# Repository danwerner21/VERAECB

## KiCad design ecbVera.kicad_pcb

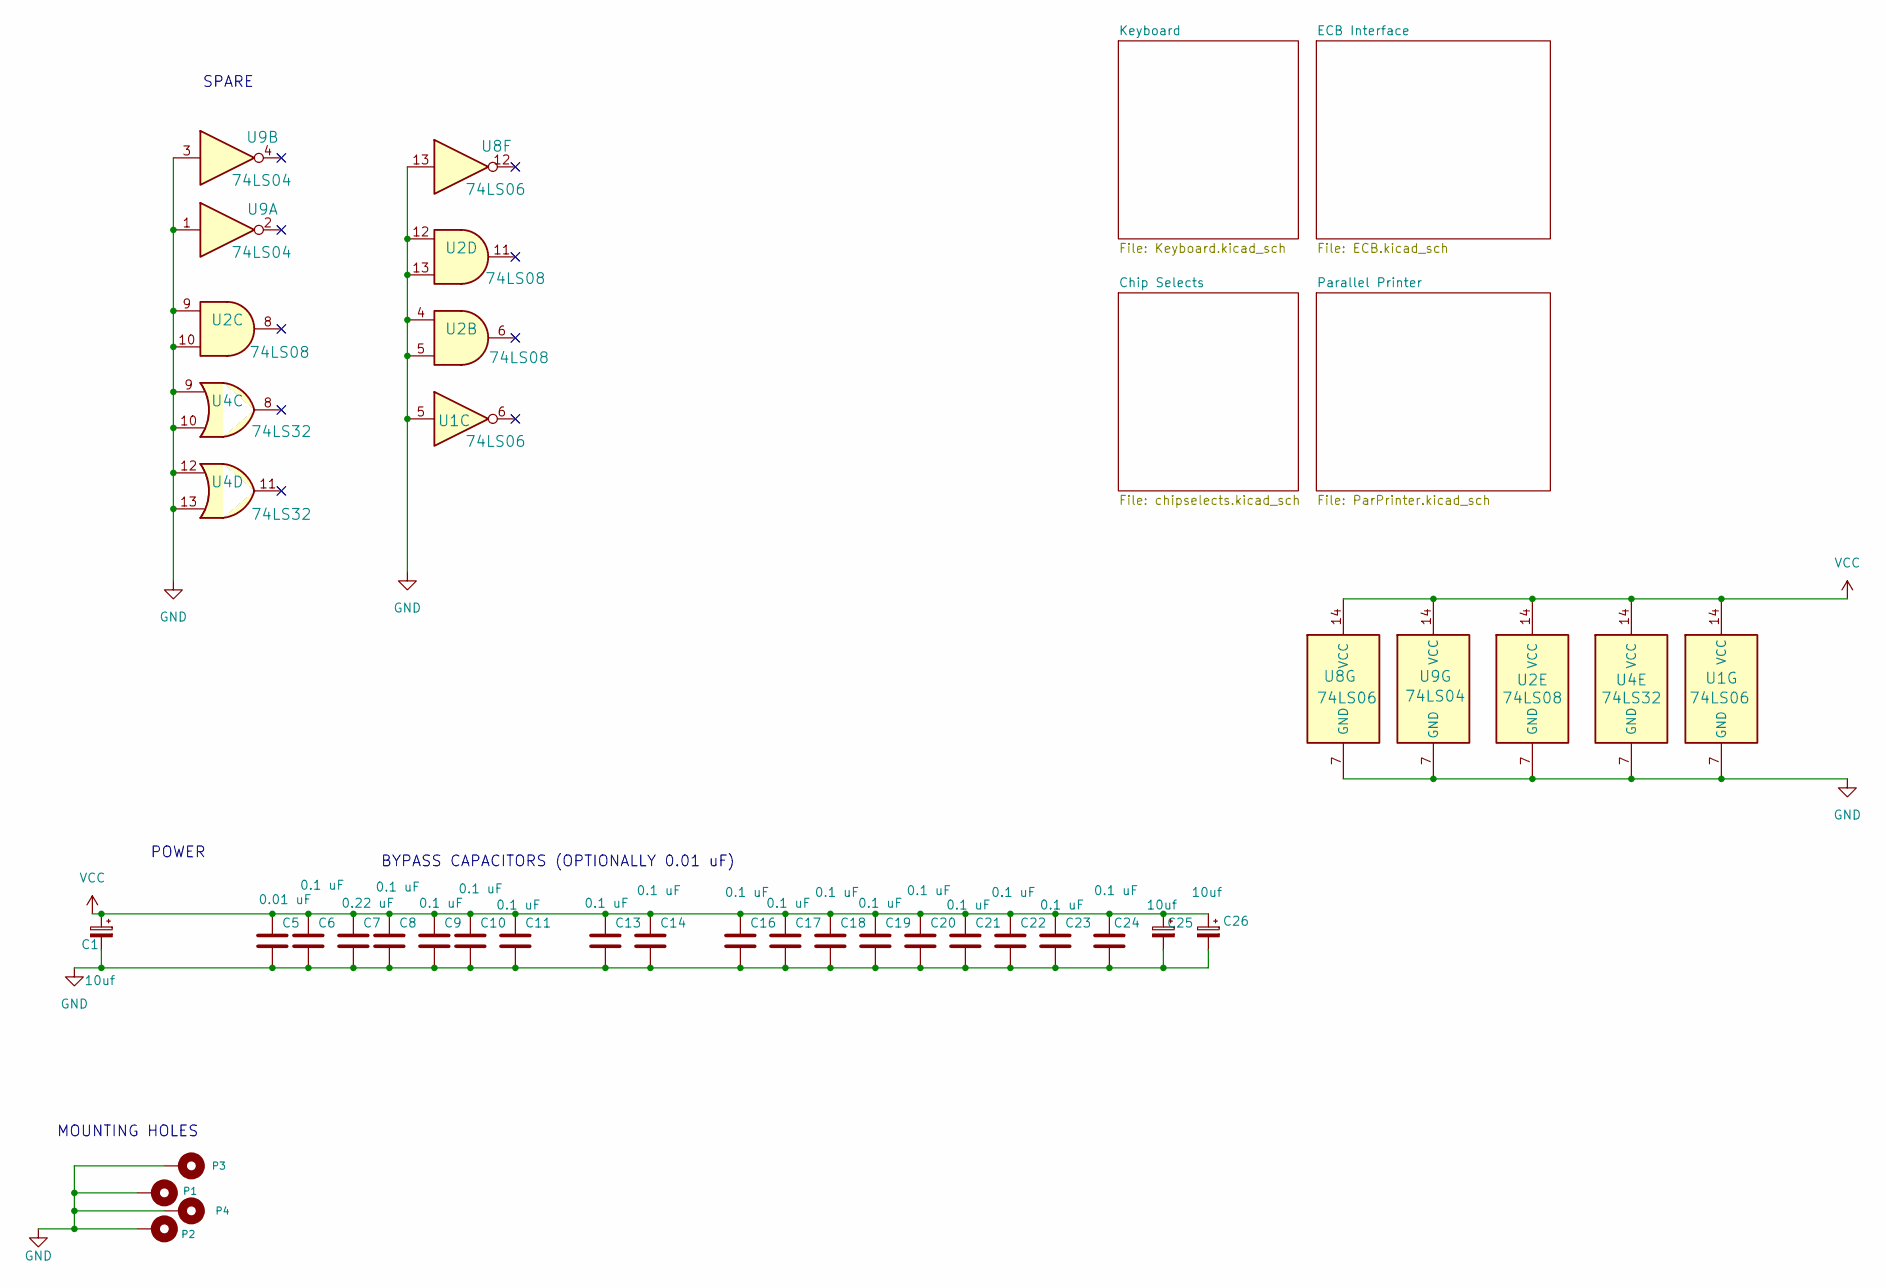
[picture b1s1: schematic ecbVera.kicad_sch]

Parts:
C1, C25, C26: 10uf; STD_DDW_PCAP
C5: 0.01 uF; STD_DDW_CAP
C6, C8, C9, C10, C11, C13, C14, C16, C17, C18, C19, C20, C21, C22, C23, C24: 0.1 uF; STD_DDW_CAP
C7: 0.22 uF; STD_DDW_CAP
P1, P2, P3, P4: MountingHole_4.3mm_M4
U1, U8: 74LS06; STD_DDW_DIP14
U2: 74LS08; STD_DDW_DIP14
U4: 74LS32; STD_DDW_DIP14
U9: 74LS04; STD_DDW_DIP14

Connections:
GND: C1.2, C5.2, C6.2, C7.2, C8.2, C9.2, C10.2, C11.2, C13.2, C14.2, C16.2, C17.2, C18.2, C19.2, C20.2, C21.2, C22.2, C23.2, C24.2, C25.2, C26.2, P1.1, P2.1, P3.1, P4.1, U1.5, U1.7 (GND), U2.4, U2.5, U2.7 (GND), U2.9, U2.10, U2.12, U2.13, U4.7 (GND), U4.9, U4.10, U4.12, U4.13, U8.7 (GND), U8.13, U9.1, U9.3, U9.7 (GND); also elsewhere on the board
VCC: C1.1, C5.1, C6.1, C7.1, C8.1, C9.1, C10.1, C11.1, C13.1, C14.1, C16.1, C17.1, C18.1, C19.1, C20.1, C21.1, C22.1, C23.1, C24.1, C25.1, C26.1, U1.14 (VCC), U2.14 (VCC), U4.14 (VCC), U8.14 (VCC), U9.14 (VCC); also elsewhere on the board

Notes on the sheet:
SPARE
MOUNTING HOLES
BYPASS CAPACITORS (OPTIONALLY 0.01 uF)
POWER

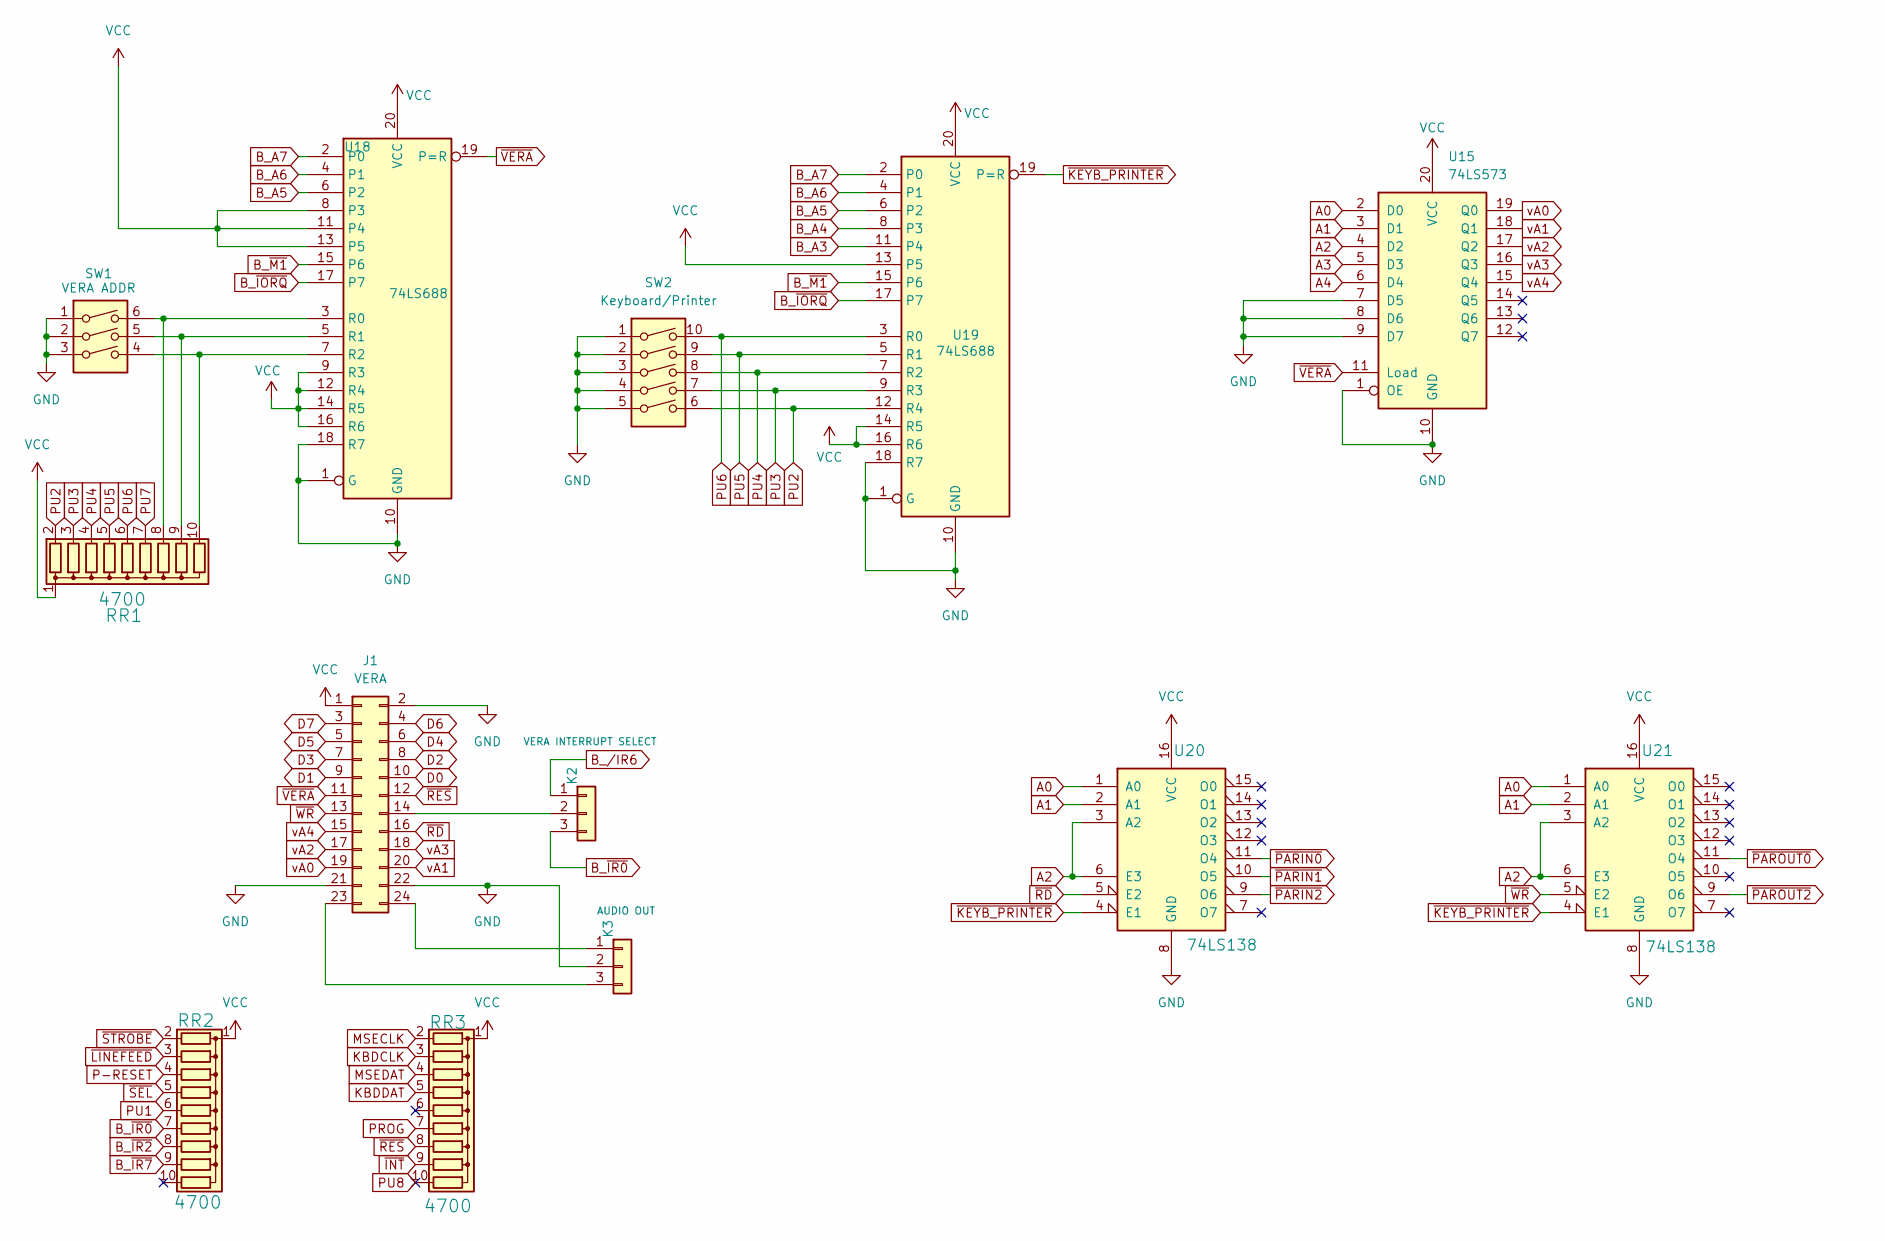
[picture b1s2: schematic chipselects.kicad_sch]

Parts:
J1: VERA; PinHeader_2x12_P2.54mm_Vertical
K2: VERA INTERRUPT SELECT; STD_DDW_PINHEAD_V_1x03
K3: AUDIO OUT; STD_DDW_PINHEAD_V_1x03
RR1, RR2, RR3: 4700; R_Array_SIP10
SW1: VERA ADDR; STD_DDW_DIP6
SW2: Keyboard/Printer; STD_DDW_DIP10
U15: 74LS573; STD_DDW_DIP20
U18, U19: 74LS688; STD_DDW_DIP20
U20, U21: 74LS138; STD_DDW_DIP16

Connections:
A0: U15.2 (D0), U20.1 (A0), U21.1 (A0); also elsewhere on the board
A1: U15.3 (D1), U20.2 (A1), U21.2 (A1); also elsewhere on the board
A2: U15.4 (D2), U20.3 (A2), U20.6 (E3), U21.3 (A2), U21.6 (E3); also elsewhere on the board
A3: U15.5 (D3); also elsewhere on the board
A4: U15.6 (D4); also elsewhere on the board
B_A3: U19.11 (P4); also elsewhere on the board
B_A4: U19.8 (P3); also elsewhere on the board
B_A5: U18.6 (P2), U19.6 (P2); also elsewhere on the board
B_A6: U18.4 (P1), U19.4 (P1); also elsewhere on the board
B_A7: U18.2 (P0), U19.2 (P0); also elsewhere on the board
B_~IORQ: U18.17 (P7), U19.17 (P7); also elsewhere on the board
B_~IR0: K2.3, RR2.7 (R6); also elsewhere on the board
B_~IR2: RR2.8 (R7); also elsewhere on the board
B_~IR7: RR2.9 (R8); also elsewhere on the board
B_~M1: U18.15 (P6), U19.15 (P6); also elsewhere on the board
D0: J1.10; also elsewhere on the board
D1: J1.9; also elsewhere on the board
D2: J1.8; also elsewhere on the board
D3: J1.7; also elsewhere on the board
D4: J1.6; also elsewhere on the board
D5: J1.5; also elsewhere on the board
D6: J1.4; also elsewhere on the board
D7: J1.3; also elsewhere on the board
GND: J1.2, J1.21, J1.22, K3.2, SW1.1, SW1.2, SW1.3, SW2.1, SW2.2, SW2.3, SW2.4, SW2.5, U15.1 (OE), U15.7 (D5), U15.8 (D6), U15.9 (D7), U15.10 (GND), U18.1 (G), U18.10 (GND), U18.18 (R7), U19.1 (G), U19.10 (GND), U19.18 (R7), U20.8 (GND), U21.8 (GND); also elsewhere on the board
KBDCLK: RR3.3 (R2); also elsewhere on the board
KBDDAT: RR3.5 (R4); also elsewhere on the board
MSECLK: RR3.2 (R1); also elsewhere on the board
MSEDAT: RR3.4 (R3); also elsewhere on the board
unnamed: J1.14, K2.2
unnamed: J1.23, K3.3
unnamed: J1.24, K3.1
unnamed: RR1.8 (R7), SW1.6, U18.3 (R0)
unnamed: RR1.9 (R8), SW1.5, U18.5 (R1)
unnamed: RR1.10 (R9), SW1.4, U18.7 (R2)
P-RESET: RR2.4 (R3); also elsewhere on the board
PROG: RR3.7 (R6); also elsewhere on the board
PU1: RR2.6 (R5); also elsewhere on the board
PU2: RR1.2 (R1), SW2.6, U19.12 (R4)
PU3: RR1.3 (R2), SW2.7, U19.9 (R3)
PU4: RR1.4 (R3), SW2.8, U19.7 (R2)
PU5: RR1.5 (R4), SW2.9, U19.5 (R1)
PU6: RR1.6 (R5), SW2.10, U19.3 (R0)
PU7: RR1.7 (R6); also elsewhere on the board
PU8: RR3.10 (R9)
VCC: J1.1, RR1.1 (common), RR2.1 (common), RR3.1 (common), U15.20 (VCC), U18.8 (P3), U18.9 (R3), U18.11 (P4), U18.12 (R4), U18.13 (P5), U18.14 (R5), U18.16 (R6), U18.20 (VCC), U19.13 (P5), U19.14 (R5), U19.16 (R6), U19.20 (VCC), U20.16 (VCC), U21.16 (VCC); also elsewhere on the board
vA0: J1.19, U15.19 (Q0)
vA1: J1.20, U15.18 (Q1)
vA2: J1.17, U15.17 (Q2)
vA3: J1.18, U15.16 (Q3)
vA4: J1.15, U15.15 (Q4)
~INT: RR3.9 (R8); also elsewhere on the board
~KEYB_PRINTER: U19.19 (P=R), U20.4 (E1), U21.4 (E1); also elsewhere on the board
~LINEFEED: RR2.3 (R2); also elsewhere on the board
~PARIN0: U20.11 (O4); also elsewhere on the board
~PARIN1: U20.10 (O5); also elsewhere on the board
~PARIN2: U20.9 (O6); also elsewhere on the board
~PAROUT0: U21.11 (O4); also elsewhere on the board
~PAROUT2: U21.9 (O6); also elsewhere on the board
~RD: J1.16, U20.5 (E2); also elsewhere on the board
~RES: J1.12, RR3.8 (R7); also elsewhere on the board
~SEL: RR2.5 (R4); also elsewhere on the board
~STROBE: RR2.2 (R1); also elsewhere on the board
~VERA: J1.11, U15.11 (Load), U18.19 (P=R); also elsewhere on the board
~WR: J1.13, U21.5 (E2); also elsewhere on the board

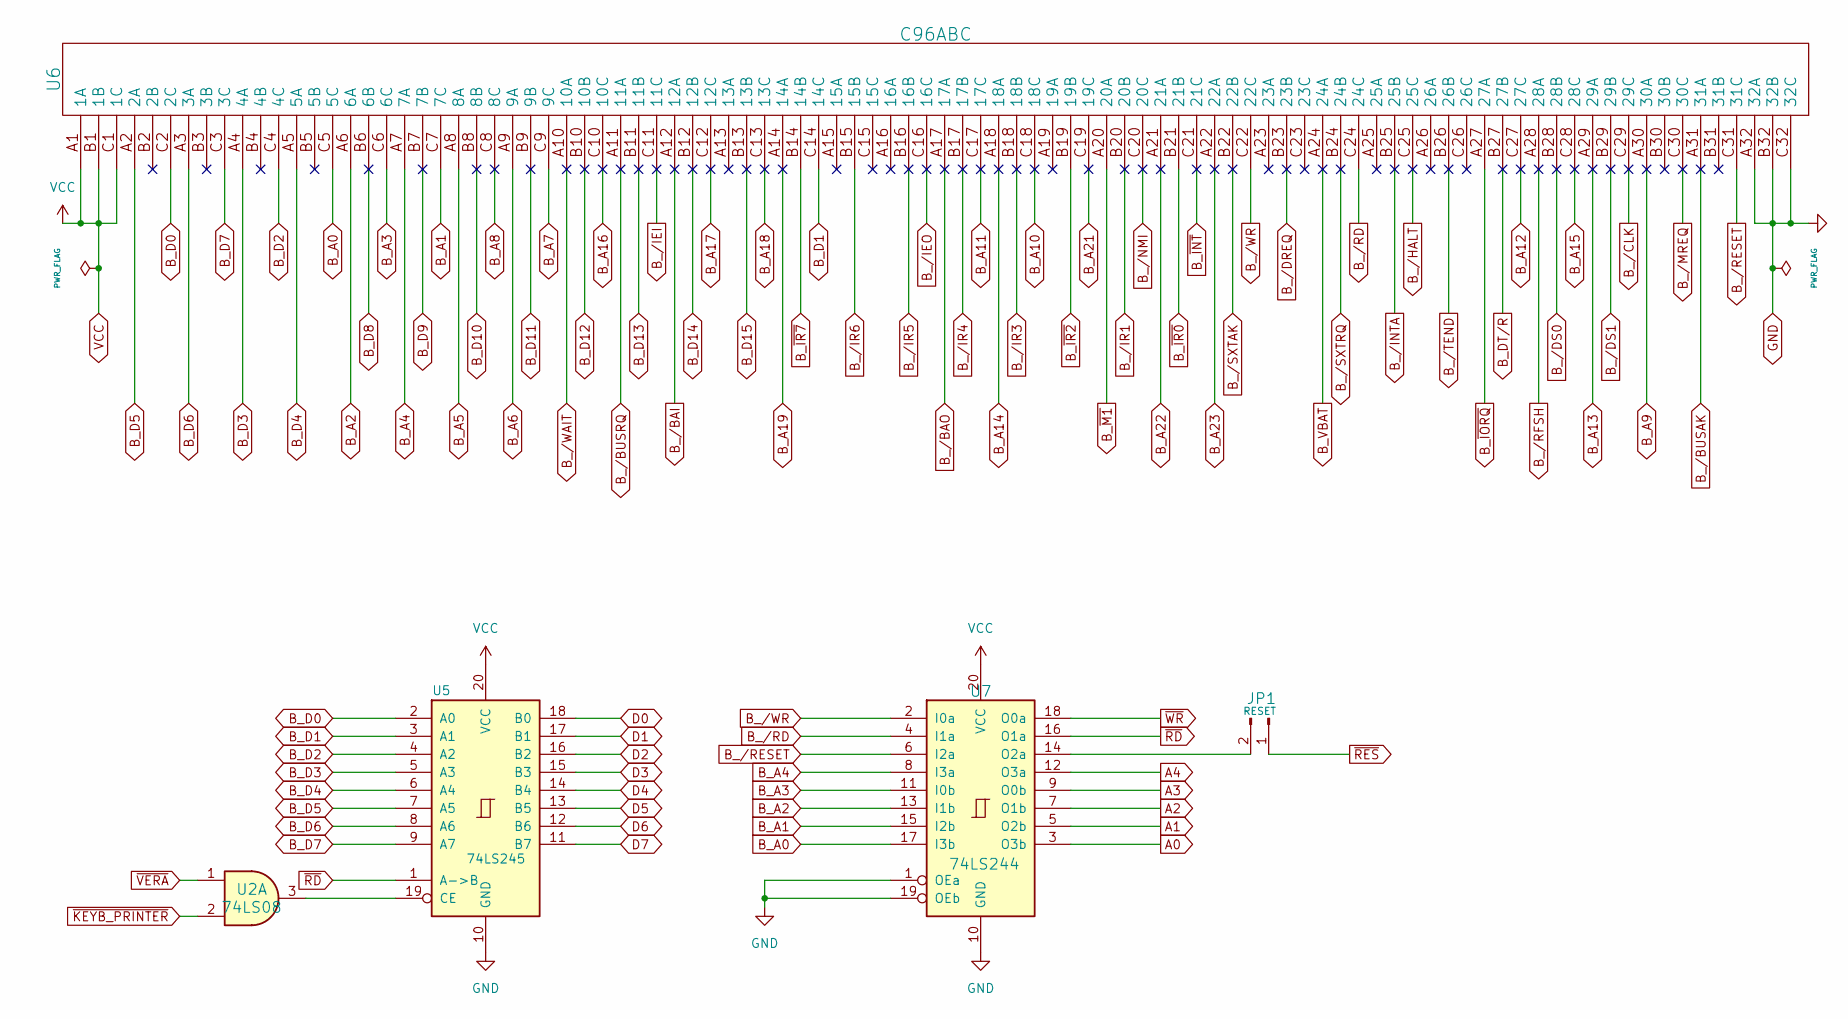
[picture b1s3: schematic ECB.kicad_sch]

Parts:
JP1: RESET; STD_DDW_PINHEAD_V_1x02
U2: 74LS08; STD_DDW_DIP14
U5: 74LS245; STD_DDW_DIP20
U6: C96ABC
U7: 74LS244; STD_DDW_DIP20

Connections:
A0: U7.3 (O3b); also elsewhere on the board
A1: U7.5 (O2b); also elsewhere on the board
A2: U7.7 (O1b); also elsewhere on the board
A3: U7.9 (O0b); also elsewhere on the board
A4: U7.12 (O3a); also elsewhere on the board
B_A0: U6.C5 (5C), U7.17 (I3b)
B_A1: U6.C7 (7C), U7.15 (I2b)
B_A2: U6.A6 (6A), U7.13 (I1b); also elsewhere on the board
B_A3: U6.C6 (6C), U7.11 (I0b); also elsewhere on the board
B_A4: U6.A7 (7A), U7.8 (I3a); also elsewhere on the board
B_A5: U6.A8 (8A); also elsewhere on the board
B_A6: U6.A9 (9A); also elsewhere on the board
B_A7: U6.C9 (9C); also elsewhere on the board
B_A8: U6.C8 (8C)
B_A9: U6.A30 (30A)
B_A10: U6.C18 (18C)
B_A11: U6.C17 (17C)
B_A12: U6.C27 (27C)
B_A13: U6.A29 (29A)
B_A14: U6.A18 (18A)
B_A15: U6.C28 (28C)
B_A16: U6.C10 (10C)
B_A17: U6.C12 (12C)
B_A18: U6.C13 (13C)
B_A19: U6.A14 (14A)
B_A21: U6.C19 (19C)
B_A22: U6.A21 (21A)
B_A23: U6.A22 (22A)
B_D0: U5.2 (A0), U6.C2 (2C)
B_D1: U5.3 (A1), U6.C14 (14C)
B_D2: U5.4 (A2), U6.C4 (4C)
B_D3: U5.5 (A3), U6.A4 (4A)
B_D4: U5.6 (A4), U6.A5 (5A)
B_D5: U5.7 (A5), U6.A2 (2A)
B_D6: U5.8 (A6), U6.A3 (3A)
B_D7: U5.9 (A7), U6.C3 (3C)
B_D8: U6.B6 (6B)
B_D9: U6.B7 (7B)
B_D10: U6.B8 (8B)
B_D11: U6.B9 (9B)
B_D12: U6.B10 (10B)
B_D13: U6.B11 (11B)
B_D14: U6.B12 (12B)
B_D15: U6.B13 (13B)
B_DT/R: U6.B27 (27B)
B_VBAT: U6.A24 (24A)
B_/BAI: U6.A12 (12A)
B_/BAO: U6.A17 (17A)
B_/BUSAK: U6.A31 (31A)
B_/BUSRQ: U6.A11 (11A)
B_/CLK: U6.C29 (29C)
B_/DREQ: U6.B23 (23B)
B_/DS0: U6.B28 (28B)
B_/DS1: U6.B29 (29B)
B_/HALT: U6.C25 (25C)
B_/IEI: U6.C11 (11C)
B_/IEO: U6.C16 (16C)
B_/INTA: U6.B25 (25B)
B_/IR1: U6.B20 (20B)
B_/IR3: U6.B18 (18B)
B_/IR4: U6.B17 (17B)
B_/IR5: U6.B16 (16B)
B_/MREQ: U6.C30 (30C)
B_/NMI: U6.C20 (20C)
B_/RFSH: U6.A28 (28A)
B_/SXTAK: U6.B22 (22B)
B_/SXTRQ: U6.B24 (24B)
B_/TEND: U6.B26 (26B)
B_/WAIT: U6.A10 (10A)
B_~INT: U6.C21 (21C)
B_~IORQ: U6.A27 (27A); also elsewhere on the board
B_~IR0: U6.B21 (21B); also elsewhere on the board
B_~IR2: U6.B19 (19B); also elsewhere on the board
B_~IR7: U6.B14 (14B); also elsewhere on the board
B_~M1: U6.A20 (20A); also elsewhere on the board
D0: U5.18 (B0); also elsewhere on the board
D1: U5.17 (B1); also elsewhere on the board
D2: U5.16 (B2); also elsewhere on the board
D3: U5.15 (B3); also elsewhere on the board
D4: U5.14 (B4); also elsewhere on the board
D5: U5.13 (B5); also elsewhere on the board
D6: U5.12 (B6); also elsewhere on the board
D7: U5.11 (B7); also elsewhere on the board
GND: U5.10 (GND), U6.A32 (32A), U6.B32 (32B), U6.C32 (32C), U7.1 (OEa), U7.10 (GND), U7.19 (OEb); also elsewhere on the board
unnamed: JP1.2, U7.14 (O2a)
unnamed: U2.3, U5.19 (CE)
VCC: U5.20 (VCC), U6.A1 (1A), U6.B1 (1B), U6.C1 (1C), U7.20 (VCC); also elsewhere on the board
~KEYB_PRINTER: U2.2; also elsewhere on the board
~RD: U5.1 (A->B), U7.16 (O1a); also elsewhere on the board
~RES: JP1.1; also elsewhere on the board
~VERA: U2.1; also elsewhere on the board
~WR: U7.18 (O0a); also elsewhere on the board

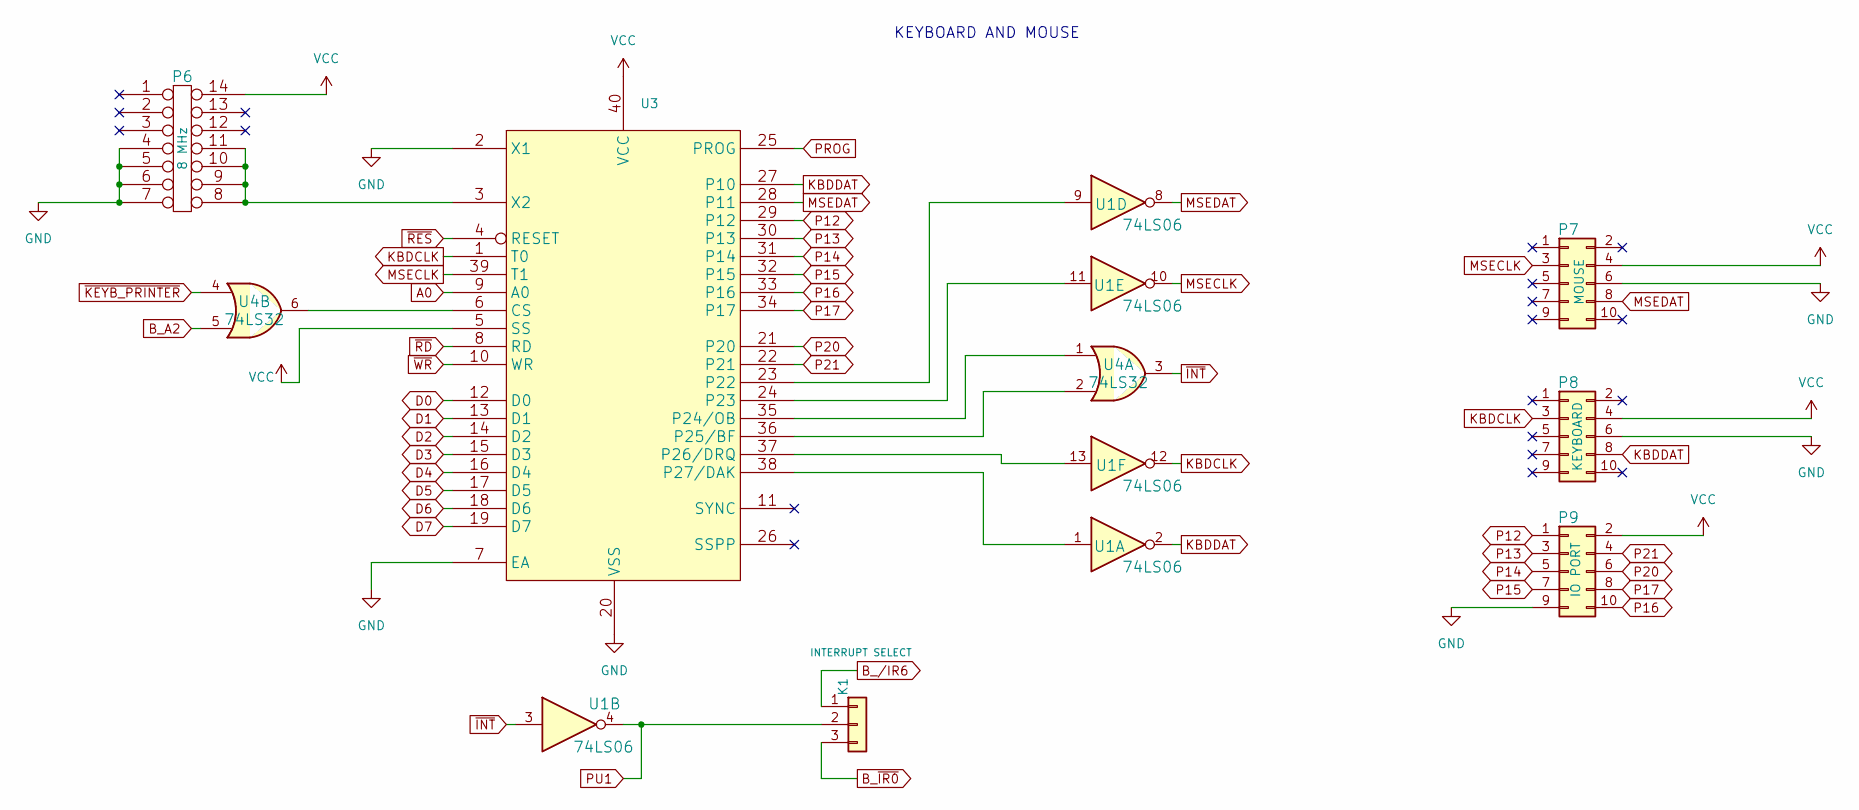
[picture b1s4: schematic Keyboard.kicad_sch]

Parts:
K1: INTERRUPT SELECT; STD_DDW_PINHEAD_V_1x03
P6: 8 MHz; STD_DDW_DIP14
P7: MOUSE; STD_DDW_PINHEAD_V_2x05
P8: KEYBOARD; STD_DDW_PINHEAD_V_2x05
P9: IO PORT; STD_DDW_PINHEAD_V_2x05
U1: 74LS06; STD_DDW_DIP14
U3: STD_DDW_DIP40
U4: 74LS32; STD_DDW_DIP14

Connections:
A0: U3.9 (A0); also elsewhere on the board
B_A2: U4.5; also elsewhere on the board
B_~IR0: K1.3; also elsewhere on the board
D0: U3.12 (D0); also elsewhere on the board
D1: U3.13 (D1); also elsewhere on the board
D2: U3.14 (D2); also elsewhere on the board
D3: U3.15 (D3); also elsewhere on the board
D4: U3.16 (D4); also elsewhere on the board
D5: U3.17 (D5); also elsewhere on the board
D6: U3.18 (D6); also elsewhere on the board
D7: U3.19 (D7); also elsewhere on the board
GND: P6.4, P6.5, P6.6, P6.7, P7.6, P8.6, P9.9, U3.2 (X1), U3.7 (EA), U3.20 (VSS); also elsewhere on the board
KBDCLK: P8.3, U1.12, U3.1 (T0); also elsewhere on the board
KBDDAT: P8.8, U1.2, U3.27 (P10); also elsewhere on the board
MSECLK: P7.3, U1.10, U3.39 (T1); also elsewhere on the board
MSEDAT: P7.8, U1.8, U3.28 (P11); also elsewhere on the board
unnamed: U3.6 (CS), U4.6
unnamed: U1.9, U3.23 (P22)
unnamed: U1.11, U3.24 (P23)
unnamed: U3.35 (P24/OB), U4.1
unnamed: U3.36 (P25/BF), U4.2
unnamed: U1.13, U3.37 (P26/DRQ)
unnamed: U1.1, U3.38 (P27/DAK)
unnamed: P6.8, P6.9, P6.10, P6.11, U3.3 (X2)
P12: P9.1, U3.29 (P12)
P13: P9.3, U3.30 (P13)
P14: P9.5, U3.31 (P14)
P15: P9.7, U3.32 (P15)
P16: P9.10, U3.33 (P16)
P17: P9.8, U3.34 (P17)
P20: P9.6, U3.21 (P20)
P21: P9.4, U3.22 (P21)
PROG: U3.25 (PROG); also elsewhere on the board
PU1: K1.2, U1.4; also elsewhere on the board
VCC: P6.14, P7.4, P8.4, P9.2, U3.5 (SS), U3.40 (VCC); also elsewhere on the board
~INT: U1.3, U4.3; also elsewhere on the board
~KEYB_PRINTER: U4.4; also elsewhere on the board
~RD: U3.8 (RD); also elsewhere on the board
~RES: U3.4 (RESET); also elsewhere on the board
~WR: U3.10 (WR); also elsewhere on the board

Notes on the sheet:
KEYBOARD AND MOUSE

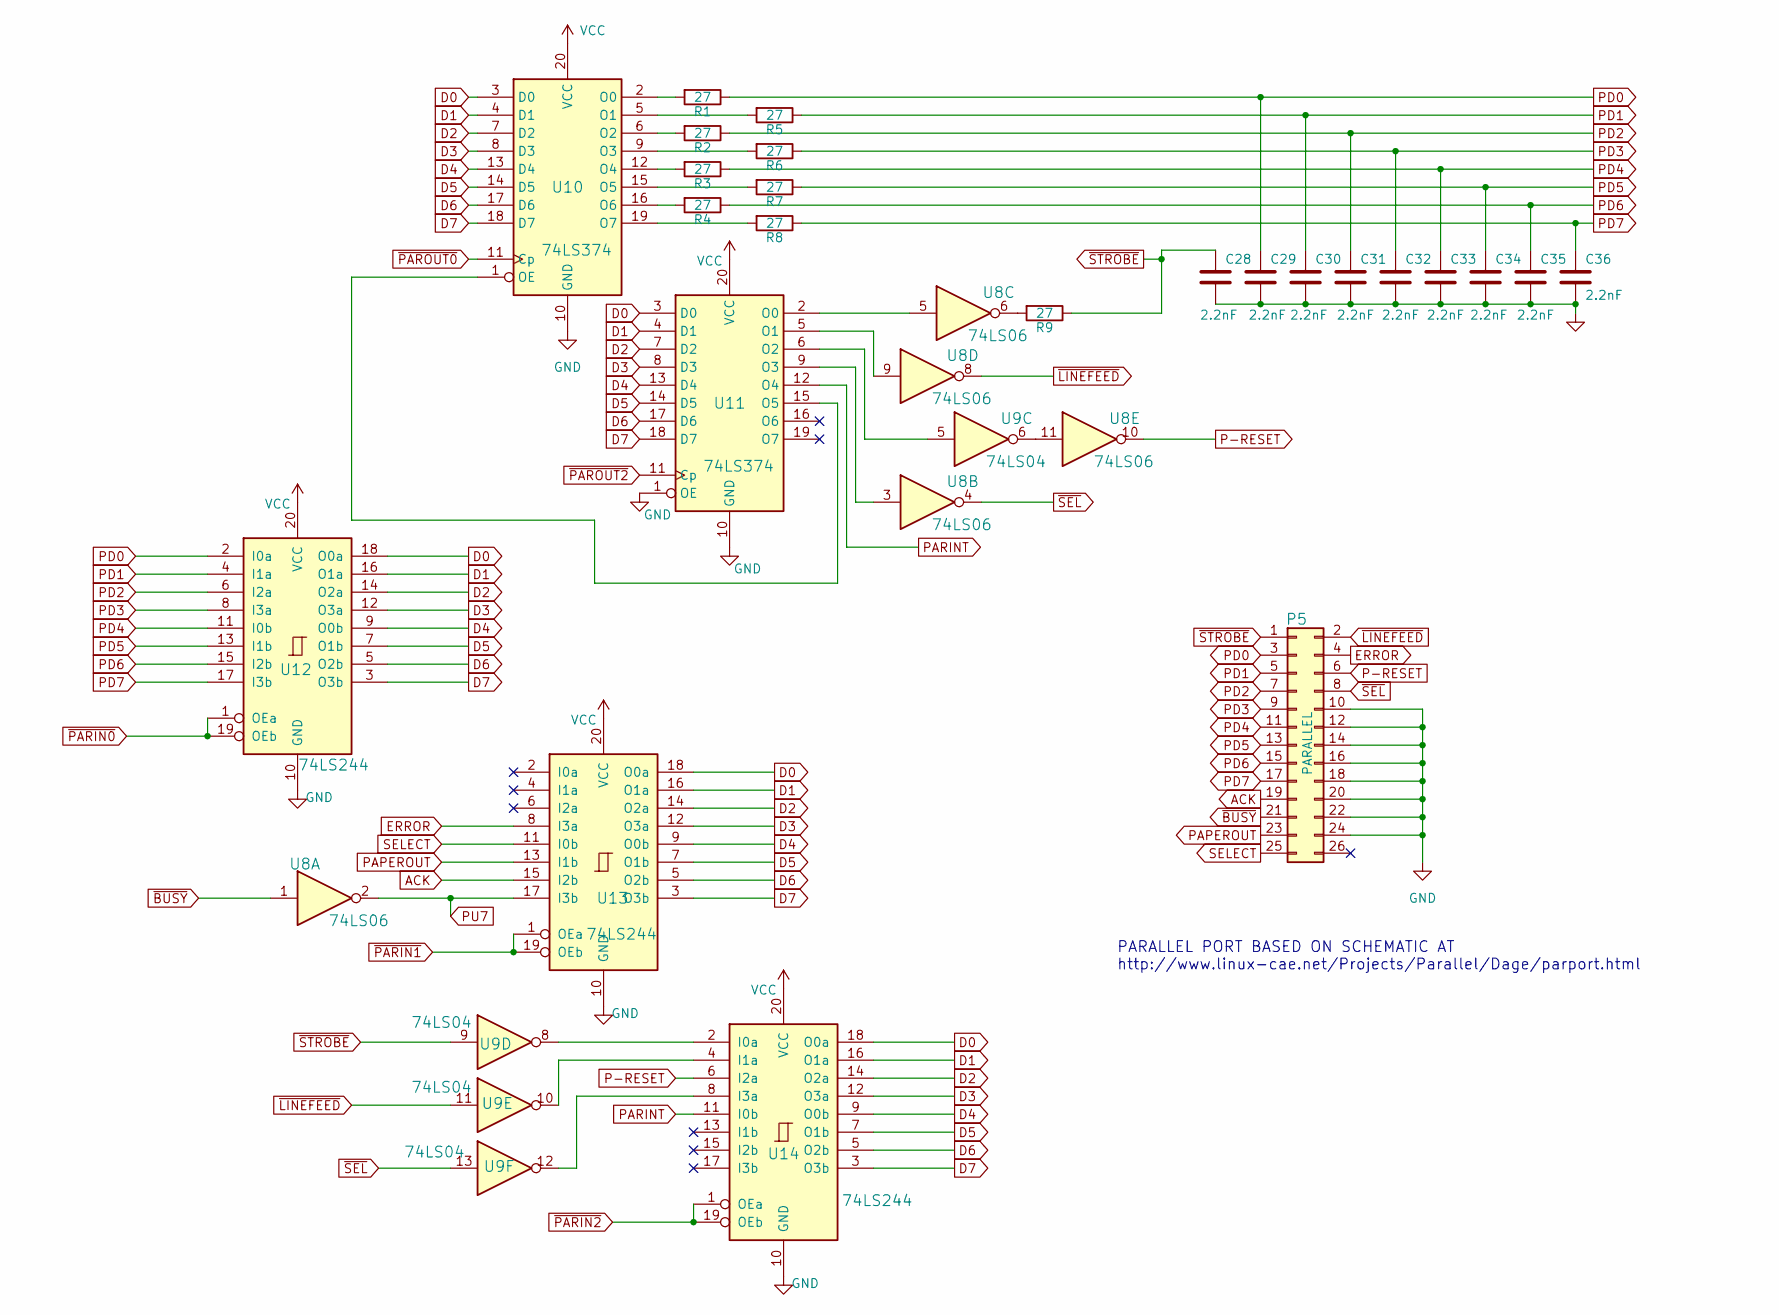
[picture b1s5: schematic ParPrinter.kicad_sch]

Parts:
C28, C29, C30, C31, C32, C33, C34, C35, C36: 2.2nF; STD_DDW_CAP
P5: PARALLEL; STD_DDW_PINHEAD_V_2x13
R1, R2, R3, R4, R5, R6, R7, R8, R9: 27; STD_DDW_RESISTOR
U8: 74LS06; STD_DDW_DIP14
U9: 74LS04; STD_DDW_DIP14
U10, U11: 74LS374; STD_DDW_DIP20
U12, U13, U14: 74LS244; STD_DDW_DIP20

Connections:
ACK: P5.19, U13.15 (I2b)
D0: U10.3 (D0), U11.3 (D0), U12.18 (O0a), U13.18 (O0a), U14.18 (O0a); also elsewhere on the board
D1: U10.4 (D1), U11.4 (D1), U12.16 (O1a), U13.16 (O1a), U14.16 (O1a); also elsewhere on the board
D2: U10.7 (D2), U11.7 (D2), U12.14 (O2a), U13.14 (O2a), U14.14 (O2a); also elsewhere on the board
D3: U10.8 (D3), U11.8 (D3), U12.12 (O3a), U13.12 (O3a), U14.12 (O3a); also elsewhere on the board
D4: U10.13 (D4), U11.13 (D4), U12.9 (O0b), U13.9 (O0b), U14.9 (O0b); also elsewhere on the board
D5: U10.14 (D5), U11.14 (D5), U12.7 (O1b), U13.7 (O1b), U14.7 (O1b); also elsewhere on the board
D6: U10.17 (D6), U11.17 (D6), U12.5 (O2b), U13.5 (O2b), U14.5 (O2b); also elsewhere on the board
D7: U10.18 (D7), U11.18 (D7), U12.3 (O3b), U13.3 (O3b), U14.3 (O3b); also elsewhere on the board
ERROR: P5.4, U13.8 (I3a)
GND: C28.2, C29.2, C30.2, C31.2, C32.2, C33.2, C34.2, C35.2, C36.2, P5.10, P5.12, P5.14, P5.16, P5.18, P5.20, P5.22, P5.24, U10.10 (GND), U11.1 (OE), U11.10 (GND), U12.10 (GND), U13.10 (GND), U14.10 (GND); also elsewhere on the board
unnamed: R9.2, U8.6
unnamed: U8.11, U9.6
unnamed: R1.2, U10.2 (O0)
unnamed: R5.2, U10.5 (O1)
unnamed: R2.2, U10.6 (O2)
unnamed: R6.2, U10.9 (O3)
unnamed: R3.2, U10.12 (O4)
unnamed: R7.2, U10.15 (O5)
unnamed: R4.2, U10.16 (O6)
unnamed: R8.2, U10.19 (O7)
unnamed: U10.1 (OE), U11.15 (O5)
unnamed: U8.5, U11.2 (O0)
unnamed: U8.9, U11.5 (O1)
unnamed: U9.5, U11.6 (O2)
unnamed: U8.3, U11.9 (O3)
unnamed: U9.8, U14.2 (I0a)
unnamed: U9.10, U14.4 (I1a)
unnamed: U9.12, U14.8 (I3a)
P-RESET: P5.6, U8.10, U14.6 (I2a); also elsewhere on the board
PAPEROUT: P5.23, U13.13 (I1b)
PARINT: U11.12 (O4), U14.11 (I0b)
PD0: C29.1, P5.3, R1.1, U12.2 (I0a)
PD1: C30.1, P5.5, R5.1, U12.4 (I1a)
PD2: C31.1, P5.7, R2.1, U12.6 (I2a)
PD3: C32.1, P5.9, R6.1, U12.8 (I3a)
PD4: C33.1, P5.11, R3.1, U12.11 (I0b)
PD5: C34.1, P5.13, R7.1, U12.13 (I1b)
PD6: C35.1, P5.15, R4.1, U12.15 (I2b)
PD7: C36.1, P5.17, R8.1, U12.17 (I3b)
PU7: U8.2, U13.17 (I3b); also elsewhere on the board
SELECT: P5.25, U13.11 (I0b)
VCC: U10.20 (VCC), U11.20 (VCC), U12.20 (VCC), U13.20 (VCC), U14.20 (VCC); also elsewhere on the board
~BUSY: P5.21, U8.1
~LINEFEED: P5.2, U8.8, U9.11; also elsewhere on the board
~PARIN0: U12.1 (OEa), U12.19 (OEb); also elsewhere on the board
~PARIN1: U13.1 (OEa), U13.19 (OEb); also elsewhere on the board
~PARIN2: U14.1 (OEa), U14.19 (OEb); also elsewhere on the board
~PAROUT0: U10.11 (Cp); also elsewhere on the board
~PAROUT2: U11.11 (Cp); also elsewhere on the board
~SEL: P5.8, U8.4, U9.13; also elsewhere on the board
~STROBE: C28.1, P5.1, R9.1, U9.9; also elsewhere on the board

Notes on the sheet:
PARALLEL PORT BASED ON SCHEMATIC AT http://www.linux-cae.net/Projects/Parallel/Dage/parport.html

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
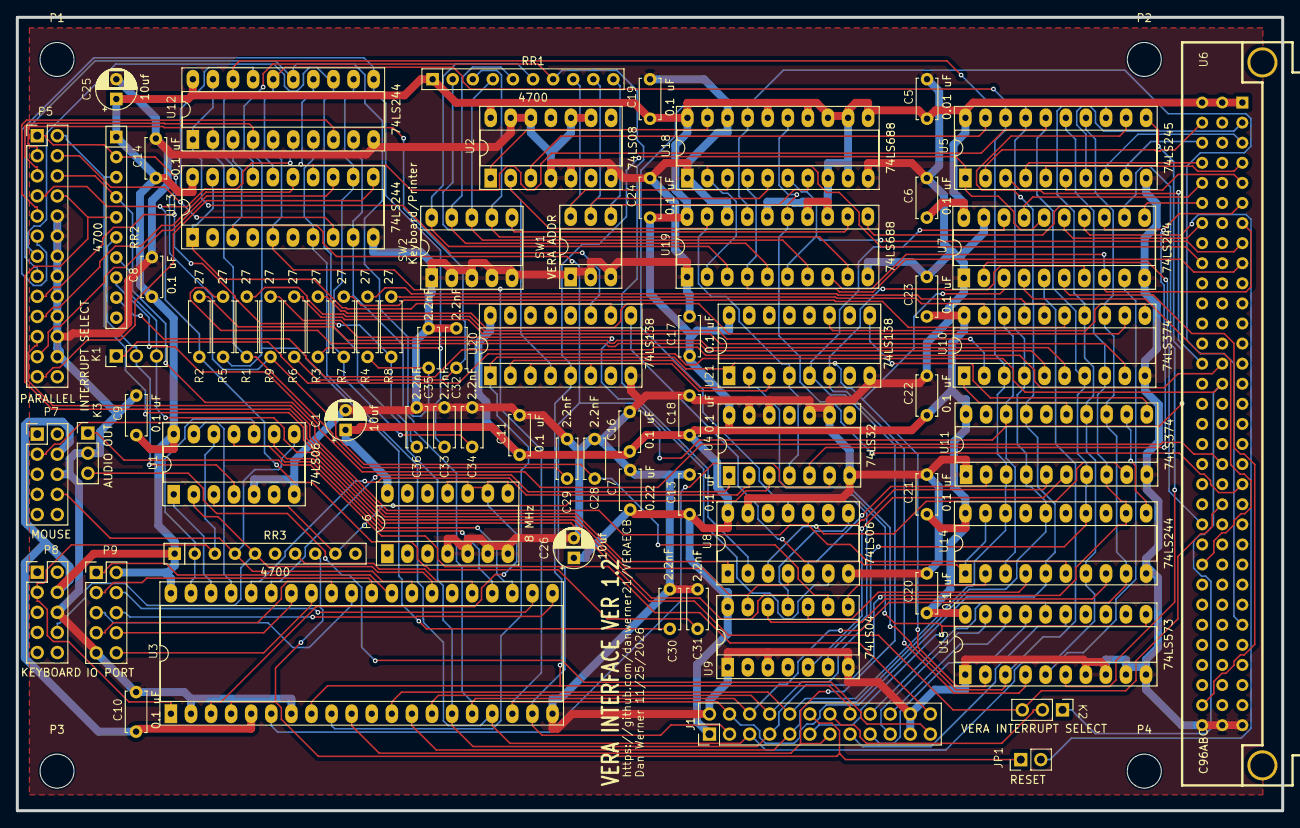
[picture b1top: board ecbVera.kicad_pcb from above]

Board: 2 copper layers, 160.0 x 100.3 mm, 77 parts (0 on the bottom side), 128 nets.
